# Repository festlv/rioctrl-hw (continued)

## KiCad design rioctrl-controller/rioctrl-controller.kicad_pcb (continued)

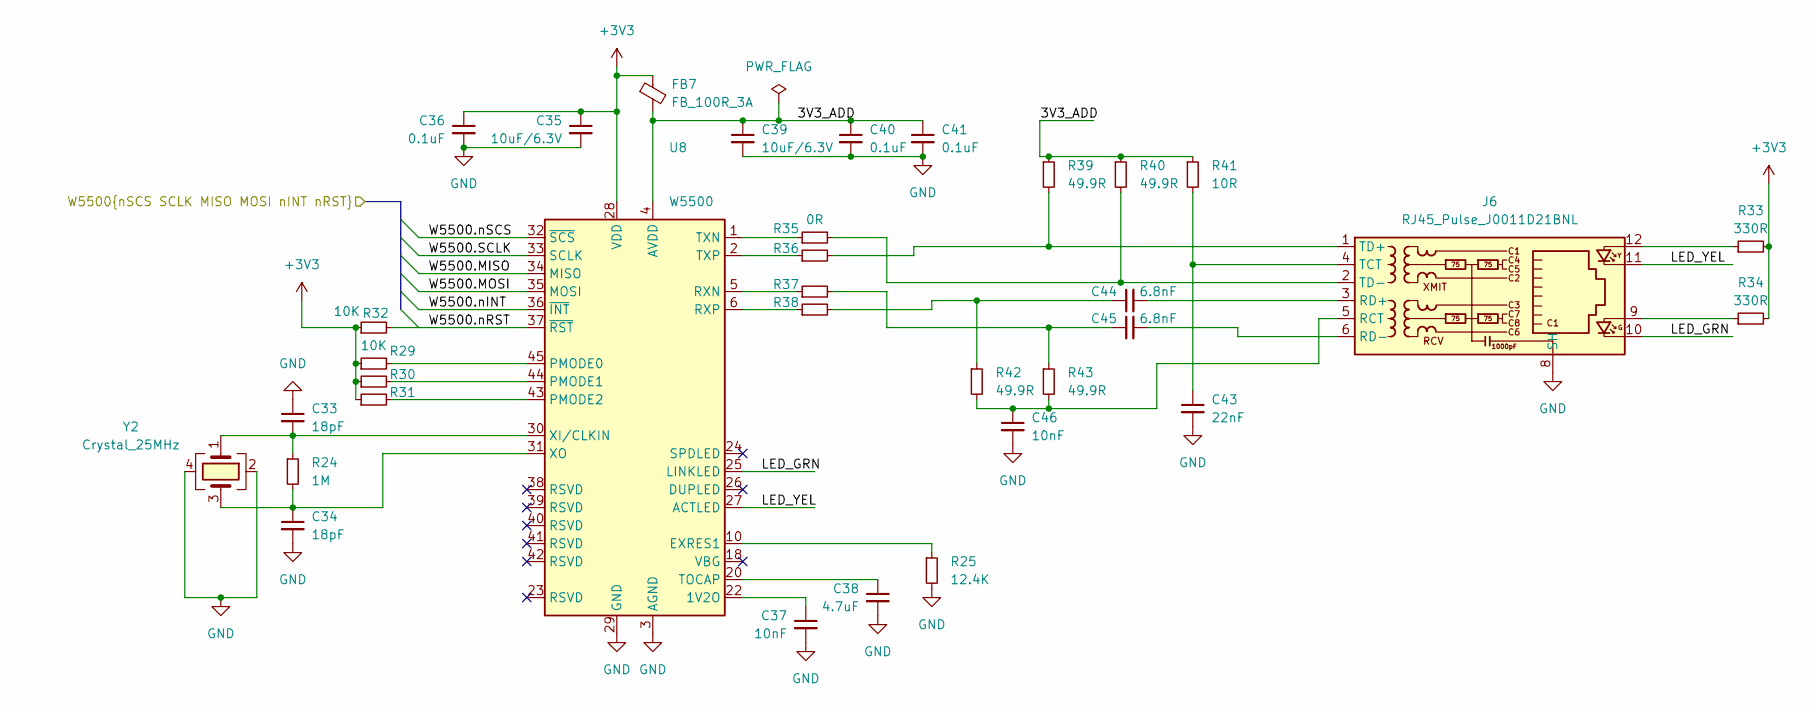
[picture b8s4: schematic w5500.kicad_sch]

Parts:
C33, C34: 18pF; C_0603_1608Metric
C35, C39: 10uF/6.3V; C_0603_1608Metric
C36, C40, C41: 0.1uF; C_0603_1608Metric
C37, C46: 10nF; C_0603_1608Metric
C38: 4.7uF; C_0603_1608Metric
C43: 22nF; C_0603_1608Metric
C44, C45: 6.8nF; C_0603_1608Metric
FB7: FB_100R_3A; L_0603_1608Metric; MPN UPZ1608E101-3R0TF; LCSC# C96995
J6: RJ45_Pulse_J0011D21BNL; RJ45_J0011D21BNL; MPN J0011D21BNL; LCSC# C455444
R24: 1M; R_0603_1608Metric
R25: 12.4K; R_0603_1608Metric
R29, R30, R31, R32: 10K; R_0603_1608Metric
R33, R34: 330R; R_0603_1608Metric
R35, R36, R37, R38: 0R; R_0603_1608Metric
R39, R40, R42, R43: 49.9R; R_0603_1608Metric
R41: 10R; R_0603_1608Metric
U8: W5500; LQFP-48_7x7mm_P0.5mm
Y2: Crystal_25MHz; Crystal_SMD_2520-4Pin_2.5x2.0mm; MPN TXM25M0004252DBCEO00T; LCSC# C284164

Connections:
+3V3: C35.1, C36.1, FB7.1, R29.1, R30.1, R31.1, R32.1, R33.2, R34.2, U8.28 (VDD); also elsewhere on the board
/FPGA/W5500.MISO: U8.34 (MISO); also elsewhere on the board
/FPGA/W5500.MOSI: U8.35 (MOSI); also elsewhere on the board
/FPGA/W5500.SCLK: U8.33 (SCLK); also elsewhere on the board
/FPGA/W5500.nINT: U8.36 (~INT); also elsewhere on the board
/FPGA/W5500.nRST: R32.2, U8.37 (~RST); also elsewhere on the board
/FPGA/W5500.nSCS: U8.32 (~SCS); also elsewhere on the board
/W5500 interface/3V3_ADD: C39.1, C40.1, C41.1, FB7.2, R39.1, R40.1, R41.1, U8.4 (AVDD), U8.8 (AVDD), U8.11 (AVDD), U8.15 (AVDD), U8.17 (AVDD), U8.21 (AVDD)
/W5500 interface/LED_GRN: J6.10, U8.25 (LINKLED)
/W5500 interface/LED_YEL: J6.11, U8.27 (ACTLED)
GND: C33.1, C34.2, C35.2, C36.2, C37.2, C38.2, C39.2, C40.2, C41.2, C43.2, C46.2, J6.8 (SH), R25.2, U8.3 (AGND), U8.9 (AGND), U8.14 (AGND), U8.16 (AGND), U8.19 (AGND), U8.29 (GND), U8.48 (AGND), Y2.2, Y2.4; also elsewhere on the board
unnamed: C44.1, R38.2, R42.1
unnamed: C45.1, R37.2, R43.1
unnamed: J6.9, R34.1
unnamed: J6.12, R33.1
unnamed: C46.1, J6.5 (RCT), R42.2, R43.2
unnamed: C44.2, J6.3 (RD+)
unnamed: C45.2, J6.6 (RD-)
unnamed: C43.1, J6.4 (TCT), R41.2
unnamed: J6.1 (TD+), R36.2, R39.2
unnamed: J6.2 (TD-), R35.2, R40.2
unnamed: C37.1, U8.22 (1V2O)
unnamed: R25.1, U8.10 (EXRES1)
unnamed: R29.2, U8.45 (PMODE0)
unnamed: R30.2, U8.44 (PMODE1)
unnamed: R31.2, U8.43 (PMODE2)
unnamed: R37.1, U8.5 (RXN)
unnamed: R38.1, U8.6 (RXP)
unnamed: C38.1, U8.20 (TOCAP)
unnamed: R35.1, U8.1 (TXN)
unnamed: R36.1, U8.2 (TXP)
unnamed: C33.2, R24.1, U8.30 (XI/CLKIN), Y2.1
unnamed: C34.1, R24.2, U8.31 (XO), Y2.3

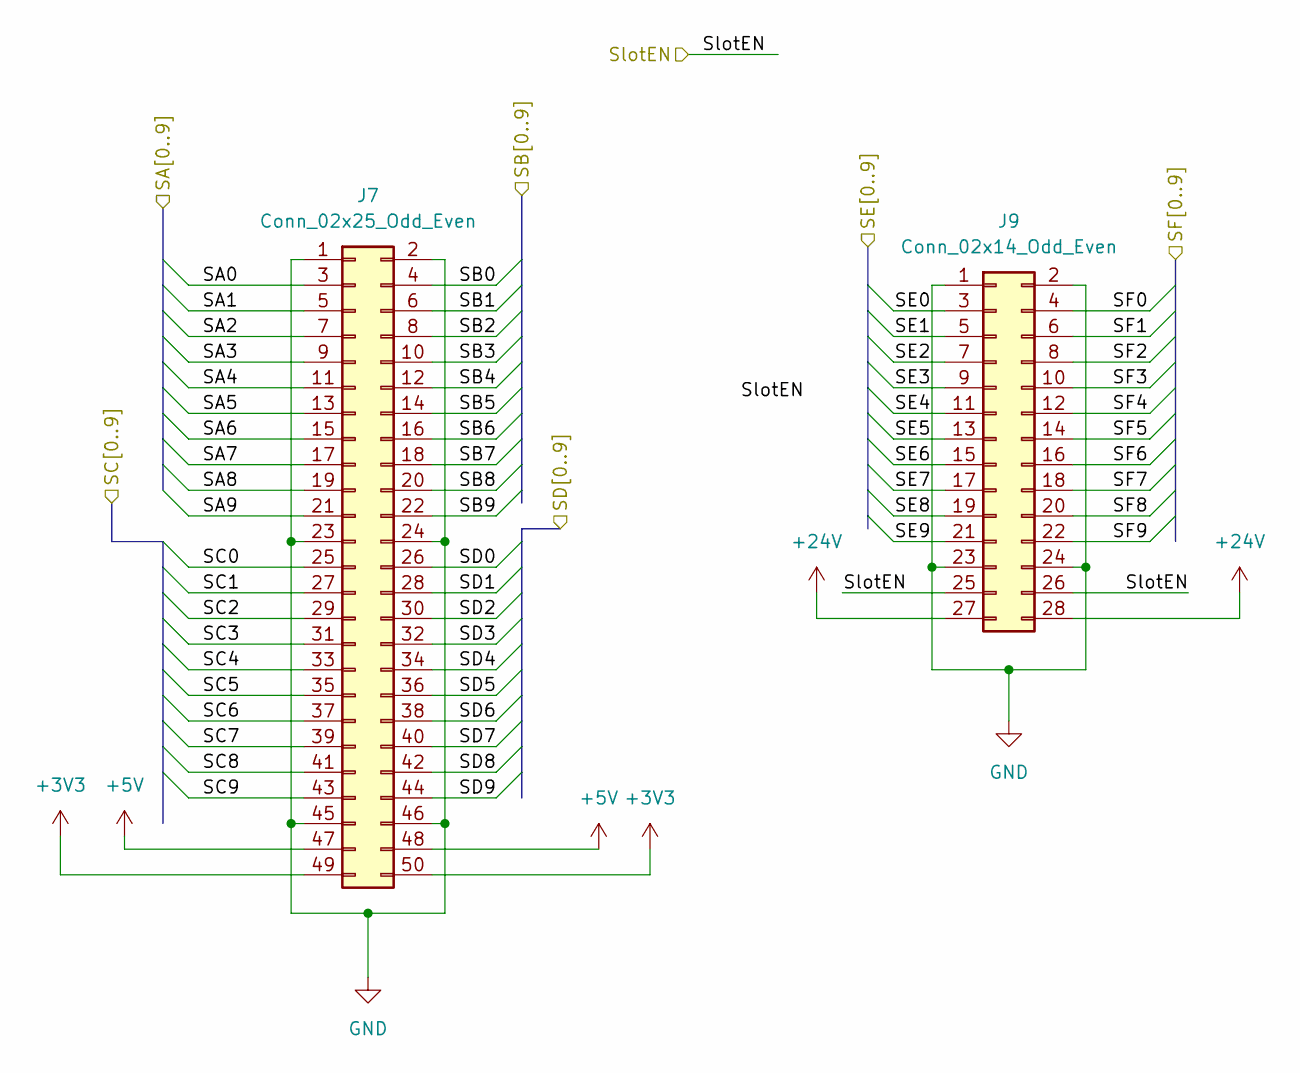
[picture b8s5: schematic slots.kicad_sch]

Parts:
J7: Conn_02x25_Odd_Even; PinSocket_2x25_P2.54mm_Vertical_SMD
J9: Conn_02x14_Odd_Even; PinSocket_2x14_P2.54mm_Vertical_SMD

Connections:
+3V3: J7.49, J7.50; also elsewhere on the board
+5V: J7.47, J7.48; also elsewhere on the board
+24V: J9.27, J9.28; also elsewhere on the board
/FPGA/SA0: J7.3; also elsewhere on the board
/FPGA/SA1: J7.5; also elsewhere on the board
/FPGA/SA2: J7.7; also elsewhere on the board
/FPGA/SA3: J7.9; also elsewhere on the board
/FPGA/SA4: J7.11; also elsewhere on the board
/FPGA/SA5: J7.13; also elsewhere on the board
/FPGA/SA6: J7.15; also elsewhere on the board
/FPGA/SA7: J7.17; also elsewhere on the board
/FPGA/SA8: J7.19; also elsewhere on the board
/FPGA/SA9: J7.21; also elsewhere on the board
/FPGA/SB0: J7.4; also elsewhere on the board
/FPGA/SB1: J7.6; also elsewhere on the board
/FPGA/SB2: J7.8; also elsewhere on the board
/FPGA/SB3: J7.10; also elsewhere on the board
/FPGA/SB4: J7.12; also elsewhere on the board
/FPGA/SB5: J7.14; also elsewhere on the board
/FPGA/SB6: J7.16; also elsewhere on the board
/FPGA/SB7: J7.18; also elsewhere on the board
/FPGA/SB8: J7.20; also elsewhere on the board
/FPGA/SB9: J7.22; also elsewhere on the board
/FPGA/SC0: J7.25; also elsewhere on the board
/FPGA/SC1: J7.27; also elsewhere on the board
/FPGA/SC2: J7.29; also elsewhere on the board
/FPGA/SC3: J7.31; also elsewhere on the board
/FPGA/SC4: J7.33; also elsewhere on the board
/FPGA/SC5: J7.35; also elsewhere on the board
/FPGA/SC6: J7.37; also elsewhere on the board
/FPGA/SC7: J7.39; also elsewhere on the board
/FPGA/SC8: J7.41; also elsewhere on the board
/FPGA/SC9: J7.43; also elsewhere on the board
/FPGA/SD0: J7.26; also elsewhere on the board
/FPGA/SD1: J7.28; also elsewhere on the board
/FPGA/SD2: J7.30; also elsewhere on the board
/FPGA/SD3: J7.32; also elsewhere on the board
/FPGA/SD4: J7.34; also elsewhere on the board
/FPGA/SD5: J7.36; also elsewhere on the board
/FPGA/SD6: J7.38; also elsewhere on the board
/FPGA/SD7: J7.40; also elsewhere on the board
/FPGA/SD8: J7.42; also elsewhere on the board
/FPGA/SD9: J7.44; also elsewhere on the board
/FPGA/SE0: J9.3; also elsewhere on the board
/FPGA/SE1: J9.5; also elsewhere on the board
/FPGA/SE2: J9.7; also elsewhere on the board
/FPGA/SE3: J9.9; also elsewhere on the board
/FPGA/SE4: J9.11; also elsewhere on the board
/FPGA/SE5: J9.13; also elsewhere on the board
/FPGA/SE6: J9.15; also elsewhere on the board
/FPGA/SE7: J9.17; also elsewhere on the board
/FPGA/SE8: J9.19; also elsewhere on the board
/FPGA/SE9: J9.21; also elsewhere on the board
/FPGA/SF0: J9.4; also elsewhere on the board
/FPGA/SF1: J9.6; also elsewhere on the board
/FPGA/SF2: J9.8; also elsewhere on the board
/FPGA/SF3: J9.10; also elsewhere on the board
/FPGA/SF4: J9.12; also elsewhere on the board
/FPGA/SF5: J9.14; also elsewhere on the board
/FPGA/SF6: J9.16; also elsewhere on the board
/FPGA/SF7: J9.18; also elsewhere on the board
/FPGA/SF8: J9.20; also elsewhere on the board
/FPGA/SF9: J9.22; also elsewhere on the board
/Slots/SlotEN: J9.25, J9.26; also elsewhere on the board
GND: J7.1, J7.2, J7.23, J7.24, J7.45, J7.46, J9.1, J9.2, J9.23, J9.24; also elsewhere on the board

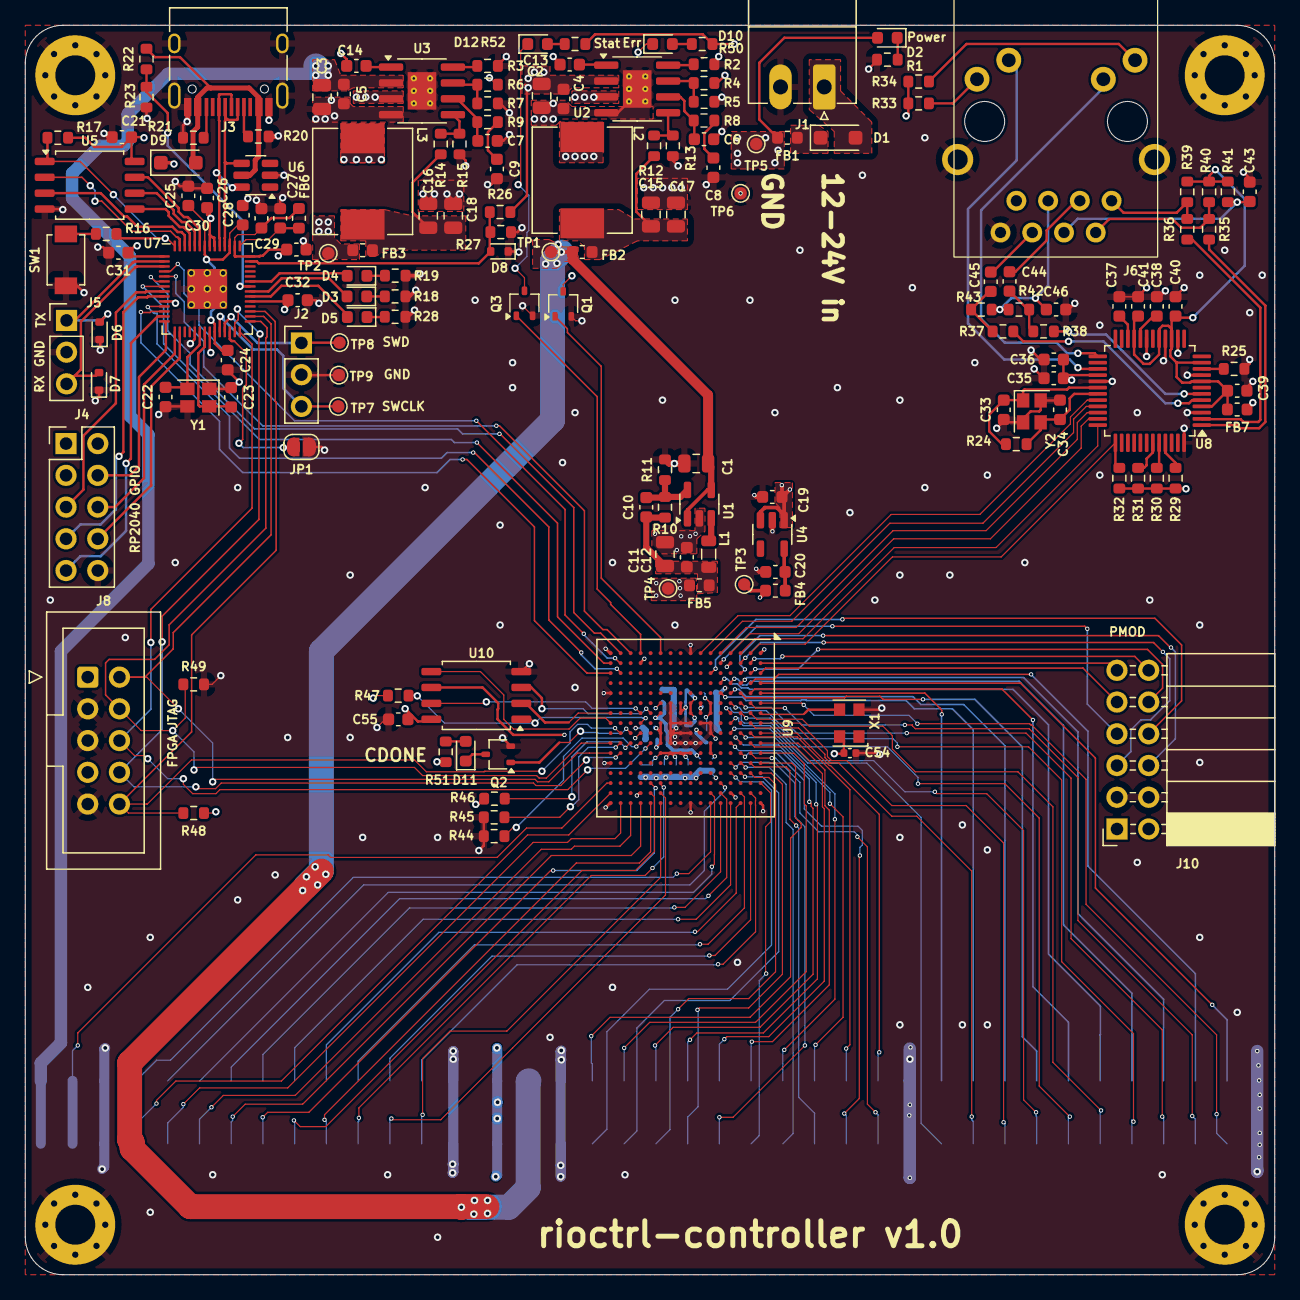
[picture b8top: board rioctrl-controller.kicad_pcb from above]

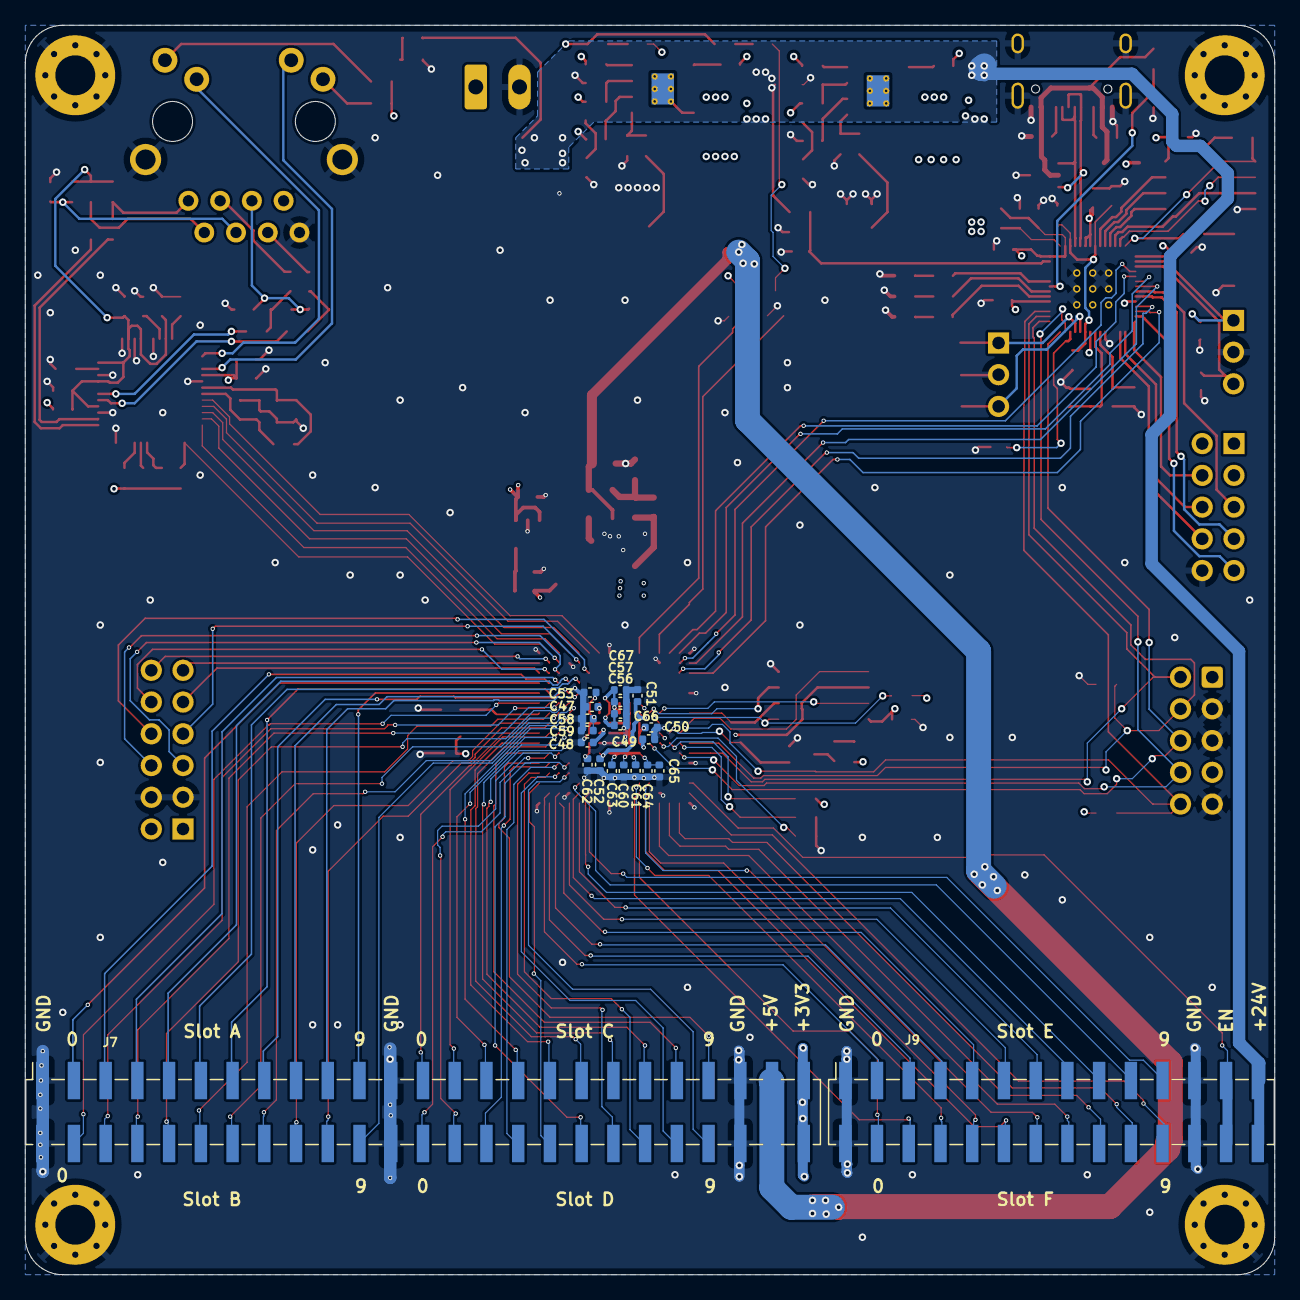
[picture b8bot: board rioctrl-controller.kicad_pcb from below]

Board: 4 copper layers, 100.0 x 100.0 mm, 181 parts (21 on the bottom side), 194 nets.

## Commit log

2024-08-17 Initial commit, controller schematic and layout done
2024-08-17 Initial schematic and layout of rioctrl-backplane
2024-08-18 Ditch the separate backplane board, increase the slot bitwidth to 12
2024-08-19 Initial schematic and layout of stepdir4
2024-08-19 rioctrl-stepdir4: pass ERC and DRC
2024-08-19 rioctrl-stepdir4: cleanup schematics
2024-08-19 Add symlinks to hadv-kicad-lib in each subdirectory
2024-08-19 Label axes on stepdir
2024-08-20 Add RJ45 screw terminal breakout, Lichuan LC10 breakout
2024-08-25 Add rioctrl-quadenc4 initial design
2024-08-25 Fix ERC, add title information to sch, add initial version of build scripts
2024-08-28 Add initial version of rioctrl-shiftio
2024-08-29 Fill in BOM (LCSC#)
2024-08-29 Add short documentation for the controller and modules
2024-08-29 Release outputs
2024-08-31 Update 3D model of RJ45 connector
2024-08-31 Update footprints for terminal blocks
2024-08-31 Regenerate outputs with more 3D models
2024-08-31 Add forgotten series resistor for 24V output transistors in rioctrl-stepdir4
2024-08-31 Add pulldown for SlotEN signal
2024-08-31 Add netlist parser to generate slot descriptions for riocore
2024-09-21 Fix minor issues in rioctrl-controller, release v1.1
2024-09-22 Update build scripts to generate ibom as well
2024-09-22 Add rioctrl-controller v1.1 outputs
2024-09-22 Release rioctrl-stepdir v1.1
2024-09-22 Add pinout documentation for rioctrl-shiftio
2024-09-22 rioctrl-shiftio: change the part number of 1 ohm resistor (previously, an 0603 resistor was specified for 0805 footprint)
2024-09-22 Add breakouts/ditron-dc11-encoder
2024-09-22 Update readme about the state of hardware
2024-09-22 Update breakouts/ditron-dc11-encoder: enlarge the PCB slightly
2024-09-25 Add pick&place position files to outputs
2024-09-25 Add license
2024-10-08 Update readme with more tested hardware
2025-03-26 Add initial spindle card design: schematics sort of done
2025-03-26 Update known issues in README
2025-03-26 rioctrl-spindle v1.0 release
2025-05-13 Add readme for spindle module
2025-10-28 fix LCSC part number and MPN for R11 and R26
